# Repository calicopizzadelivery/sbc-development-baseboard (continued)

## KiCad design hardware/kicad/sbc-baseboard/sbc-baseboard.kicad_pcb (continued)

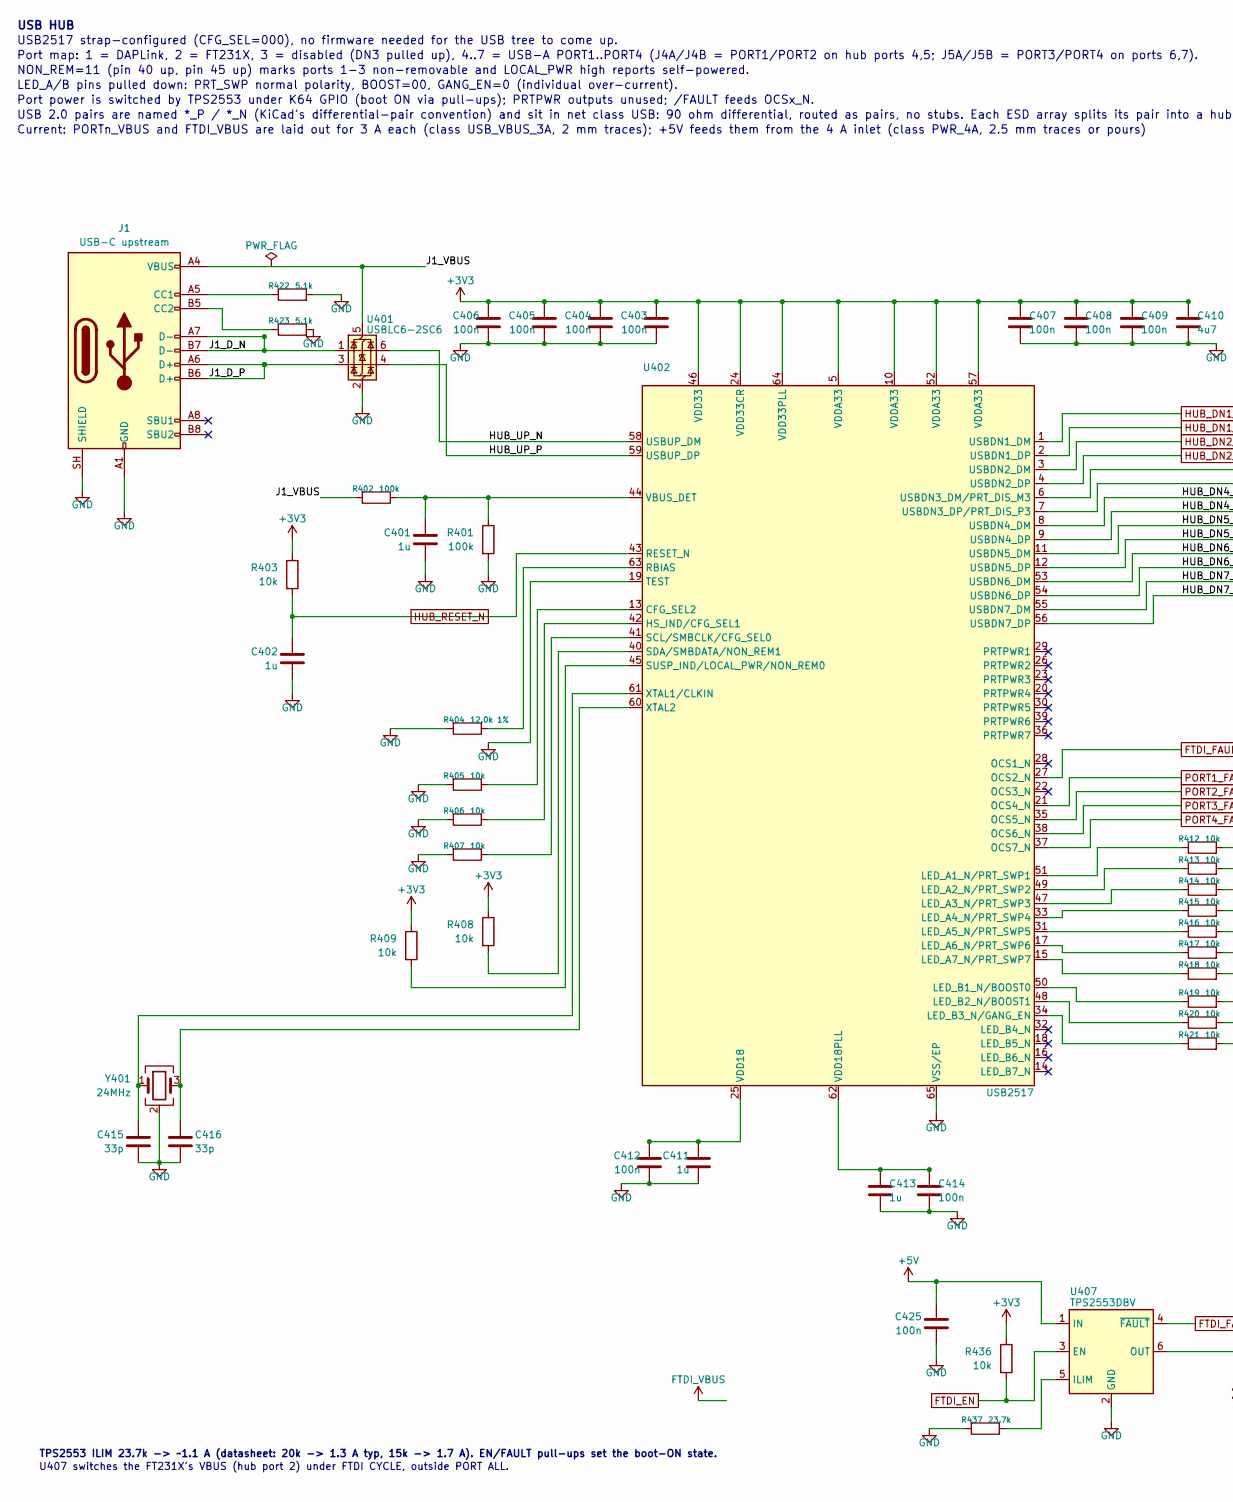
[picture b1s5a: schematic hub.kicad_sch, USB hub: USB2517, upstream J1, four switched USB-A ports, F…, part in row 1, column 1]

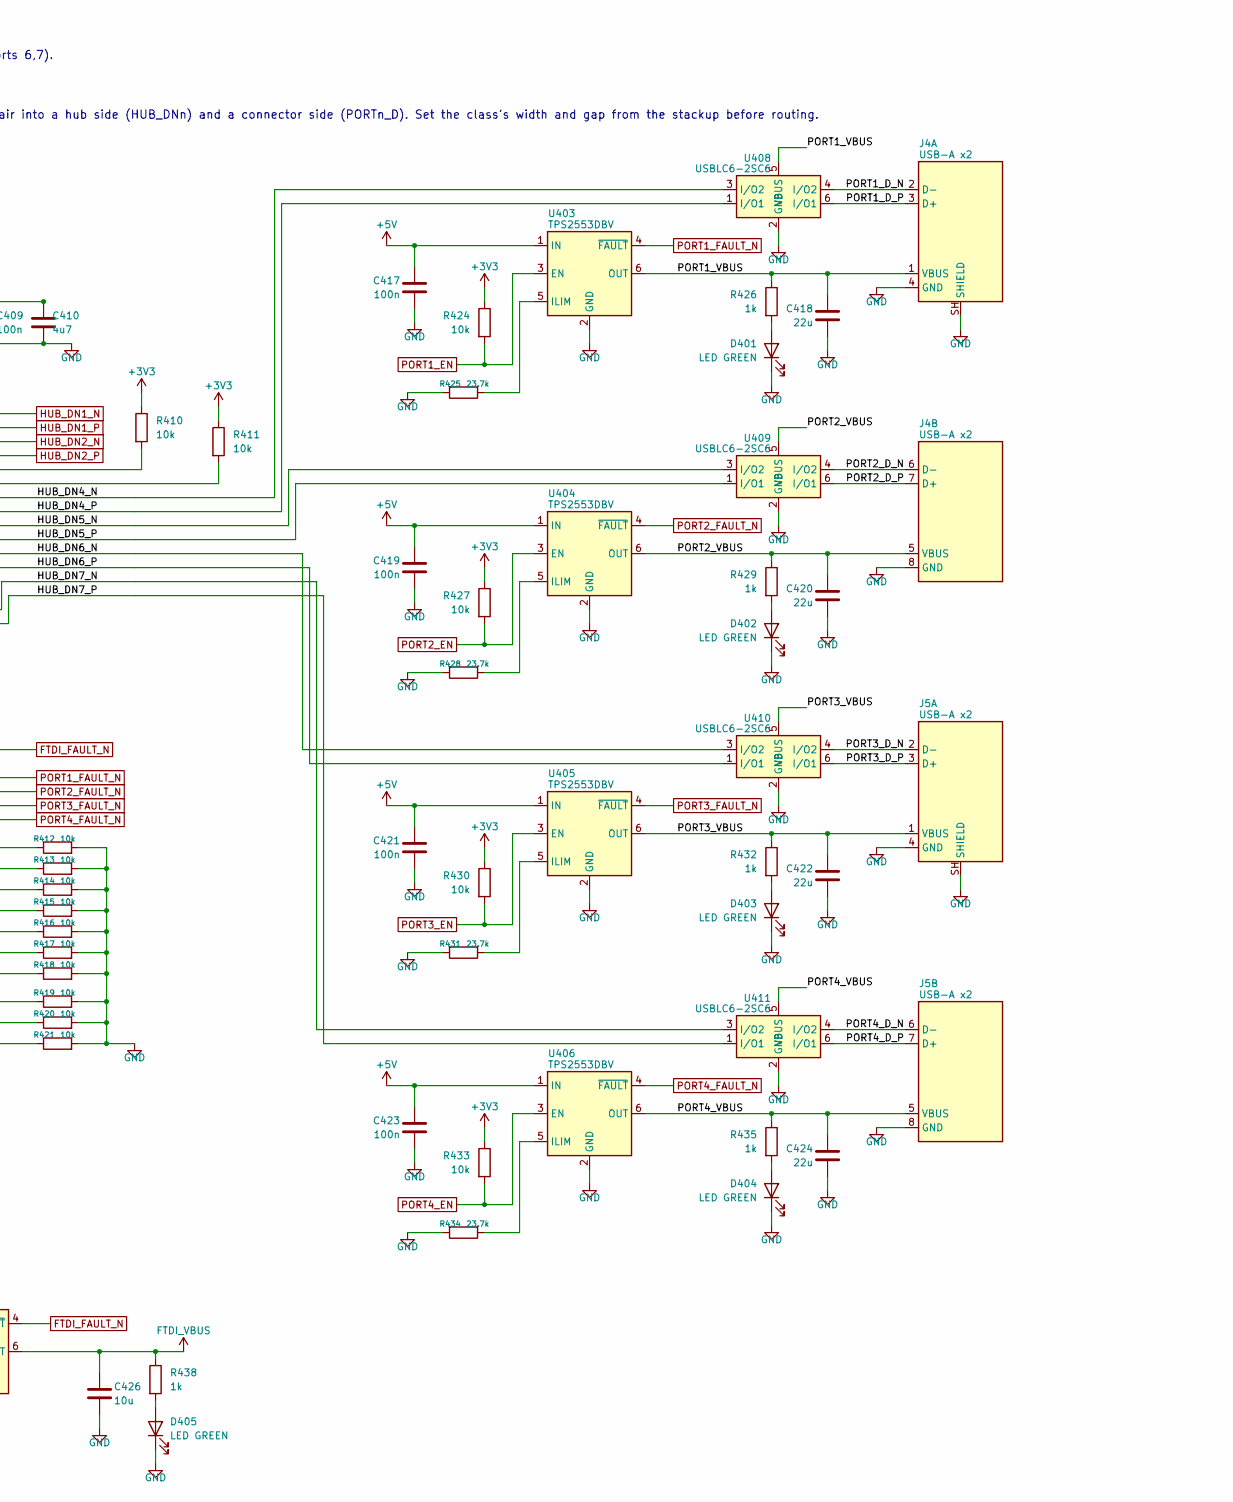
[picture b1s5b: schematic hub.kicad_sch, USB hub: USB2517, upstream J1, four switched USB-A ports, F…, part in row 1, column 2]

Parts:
C401, C402, C411, C413: 1u; C_0603_1608Metric
C403, C404, C405, C406, C407, C408, C409, C412, C414, C417, C419, C421, C423, C425: 100n; C_0603_1608Metric
C410: 4u7; C_0805_2012Metric
C415, C416: 33p; C_0603_1608Metric
C418, C420, C422, C424: 22u; C_1206_3216Metric
C426: 10u; C_0805_2012Metric
D401, D402, D403, D404, D405: LED GREEN; LED_0603_1608Metric
J1: USB-C upstream; USB_C_Receptacle_GCT_USB4105-xx-A_16P_TopMnt_Horizontal_Peg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
J4, J5: USB-A x2; USB_A_Wuerth_61400826021_Horizontal_Stacked
R401, R402: 100k; R_0603_1608Metric
R403, R405, R406, R407, R408, R409, R410, R411, R412, R413, R414, R415, R416, R417, R418, R419, R420, R421, R424, R427, R430, R433, R436: 10k; R_0603_1608Metric
R404: 12.0k 1%; R_0603_1608Metric
R422, R423: 5.1k; R_0603_1608Metric
R425, R428, R431, R434, R437: 23.7k; R_0603_1608Metric
R426, R429, R432, R435, R438: 1k; R_0603_1608Metric
U401, U408, U409, U410, U411: USBLC6-2SC6; SOT-23-6
U402: USB2517; QFN-64-1EP_9x9mm_P0.5mm_EP7.15x7.15mm
U403, U404, U405, U406, U407: TPS2553DBV; SOT-23-6
Y401: 24MHz; Crystal_SMD_3225-4Pin_3.2x2.5mm

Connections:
/USB hub/HUB_DN4_N: U402.8 (USBDN4_DM), U408.3 (I/O2)
/USB hub/HUB_DN4_P: U402.9 (USBDN4_DP), U408.1 (I/O1)
/USB hub/HUB_DN5_N: U402.11 (USBDN5_DM), U409.3 (I/O2)
/USB hub/HUB_DN5_P: U402.12 (USBDN5_DP), U409.1 (I/O1)
/USB hub/HUB_DN6_N: U402.53 (USBDN6_DM), U410.3 (I/O2)
/USB hub/HUB_DN6_P: U402.54 (USBDN6_DP), U410.1 (I/O1)
/USB hub/HUB_DN7_N: U402.55 (USBDN7_DM), U411.3 (I/O2)
/USB hub/HUB_DN7_P: U402.56 (USBDN7_DP), U411.1 (I/O1)
/USB hub/HUB_UP_N: U401.6 (I/O1), U402.58 (USBUP_DM)
/USB hub/HUB_UP_P: U401.4 (I/O2), U402.59 (USBUP_DP)
/USB hub/J1_D_N: J1.A7 (D-), J1.B7 (D-), U401.1 (I/O1)
/USB hub/J1_D_P: J1.A6 (D+), J1.B6 (D+), U401.3 (I/O2)
/USB hub/J1_VBUS: J1.A4 (VBUS), J1.A9 (VBUS), J1.B4 (VBUS), J1.B9 (VBUS), R402.2, U401.5 (VBUS)
/USB hub/PORT1_D_N: J4.2 (D-), U408.4 (I/O2)
/USB hub/PORT1_D_P: J4.3 (D+), U408.6 (I/O1)
/USB hub/PORT1_VBUS: C418.1, J4.1 (VBUS), R426.1, U403.6 (OUT), U408.5 (VBUS)
/USB hub/PORT2_D_N: J4.6 (D-), U409.4 (I/O2)
/USB hub/PORT2_D_P: J4.7 (D+), U409.6 (I/O1)
/USB hub/PORT2_VBUS: C420.1, J4.5 (VBUS), R429.1, U404.6 (OUT), U409.5 (VBUS)
/USB hub/PORT3_D_N: J5.2 (D-), U410.4 (I/O2)
/USB hub/PORT3_D_P: J5.3 (D+), U410.6 (I/O1)
/USB hub/PORT3_VBUS: C422.1, J5.1 (VBUS), R432.1, U405.6 (OUT), U410.5 (VBUS)
/USB hub/PORT4_D_N: J5.6 (D-), U411.4 (I/O2)
/USB hub/PORT4_D_P: J5.7 (D+), U411.6 (I/O1)
/USB hub/PORT4_VBUS: C424.1, J5.5 (VBUS), R435.1, U406.6 (OUT), U411.5 (VBUS)
FTDI_EN: R436.2, U407.3 (EN); also elsewhere on the board
FTDI_FAULT_N: U402.27 (OCS2_N), U407.4 (~FAULT); also elsewhere on the board
FTDI_VBUS: C426.1, R438.1, U407.6 (OUT); also elsewhere on the board
HUB_DN1_N: U402.1 (USBDN1_DM); also elsewhere on the board
HUB_DN1_P: U402.2 (USBDN1_DP); also elsewhere on the board
HUB_DN2_N: U402.3 (USBDN2_DM); also elsewhere on the board
HUB_DN2_P: U402.4 (USBDN2_DP); also elsewhere on the board
HUB_RESET_N: C402.1, R403.2, U402.43 (RESET_N); also elsewhere on the board
unnamed: D401.2 (A), R426.2
unnamed: D402.2 (A), R429.2
unnamed: D403.2 (A), R432.2
unnamed: D404.2 (A), R435.2
unnamed: D405.2 (A), R438.2
unnamed: J1.A5 (CC1), R422.1
unnamed: J1.B5 (CC2), R423.1
unnamed: R405.1, U402.13 (CFG_SEL2)
unnamed: R406.1, U402.42 (HS_IND/CFG_SEL1)
unnamed: R412.1, U402.51 (LED_A1_N/PRT_SWP1)
unnamed: R413.1, U402.49 (LED_A2_N/PRT_SWP2)
unnamed: R414.1, U402.47 (LED_A3_N/PRT_SWP3)
unnamed: R415.1, U402.33 (LED_A4_N/PRT_SWP4)
unnamed: R416.1, U402.31 (LED_A5_N/PRT_SWP5)
unnamed: R417.1, U402.17 (LED_A6_N/PRT_SWP6)
unnamed: R418.1, U402.15 (LED_A7_N/PRT_SWP7)
unnamed: R419.1, U402.50 (LED_B1_N/BOOST0)
unnamed: R420.1, U402.48 (LED_B2_N/BOOST1)
unnamed: R421.1, U402.34 (LED_B3_N/GANG_EN)
unnamed: R404.1, U402.63 (RBIAS)
unnamed: R407.1, U402.41 (SCL/SMBCLK/CFG_SEL0)
unnamed: R408.2, U402.40 (SDA/SMBDATA/NON_REM1)
unnamed: R409.2, U402.45 (SUSP_IND/LOCAL_PWR/NON_REM0)
unnamed: R410.2, U402.6 (USBDN3_DM/PRT_DIS_M3)
unnamed: R411.2, U402.7 (USBDN3_DP/PRT_DIS_P3)
unnamed: C401.1, R401.1, R402.1, U402.44 (VBUS_DET)
unnamed: C411.1, C412.1, U402.25 (VDD18)
unnamed: C413.1, C414.1, U402.62 (VDD18PLL)
unnamed: C415.1, U402.61 (XTAL1/CLKIN), Y401.1
unnamed: C416.1, U402.60 (XTAL2), Y401.3
unnamed: R425.1, U403.5 (ILIM)
unnamed: R428.1, U404.5 (ILIM)
unnamed: R431.1, U405.5 (ILIM)
unnamed: R434.1, U406.5 (ILIM)
unnamed: R437.1, U407.5 (ILIM)
PORT1_EN: R424.2, U403.3 (EN); also elsewhere on the board
PORT1_FAULT_N: U402.21 (OCS4_N), U403.4 (~FAULT); also elsewhere on the board
PORT2_EN: R427.2, U404.3 (EN); also elsewhere on the board
PORT2_FAULT_N: U402.35 (OCS5_N), U404.4 (~FAULT); also elsewhere on the board
PORT3_EN: R430.2, U405.3 (EN); also elsewhere on the board
PORT3_FAULT_N: U402.38 (OCS6_N), U405.4 (~FAULT); also elsewhere on the board
PORT4_EN: R433.2, U406.3 (EN); also elsewhere on the board
PORT4_FAULT_N: U402.37 (OCS7_N), U406.4 (~FAULT); also elsewhere on the board

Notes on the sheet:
USB HUB
USB2517 strap-configured (CFG_SEL=000), no firmware needed for the USB tree to come up.
Port map: 1 = DAPLink, 2 = FT231X, 3 = disabled (DN3 pulled up), 4..7 = USB-A PORT1..PORT4 (J4A/J4B = PORT1/PORT2 on hub ports 4,5; J5A/J5B = PORT3/PORT4 on ports 6,7).
NON_REM=11 (pin 40 up, pin 45 up) marks ports 1-3 non-removable and LOCAL_PWR high reports self-powered.
LED_A/B pins pulled down: PRT_SWP normal polarity, BOOST=00, GANG_EN=0 (individual over-current).
Port power is switched by TPS2553 under K64 GPIO (boot ON via pull-ups); PRTPWR outputs unused; /FAULT feeds OCSx_N.
USB 2.0 pairs are named *_P / *_N (KiCad's differential-pair convention) and sit in net class USB: 90 ohm differential, routed as pairs, no stubs. Each ESD array splits its pair into a hub side (HUB_DNn) and a connector side (PORTn_D). Set the class's width and gap from the stackup before routing.
Current: PORTn_VBUS and FTDI_VBUS are laid out for 3 A each (class USB_VBUS_3A, 2 mm traces); +5V feeds them from the 4 A inlet (class PWR_4A, 2.5 mm traces or pours)
TPS2553 ILIM 23.7k -> ~1.1 A (datasheet: 20k -> 1.3 A typ, 15k -> 1.7 A). EN/FAULT pull-ups set the boot-ON state.
U407 switches the FT231X's VBUS (hub port 2) under FTDI CYCLE, outside PORT ALL.

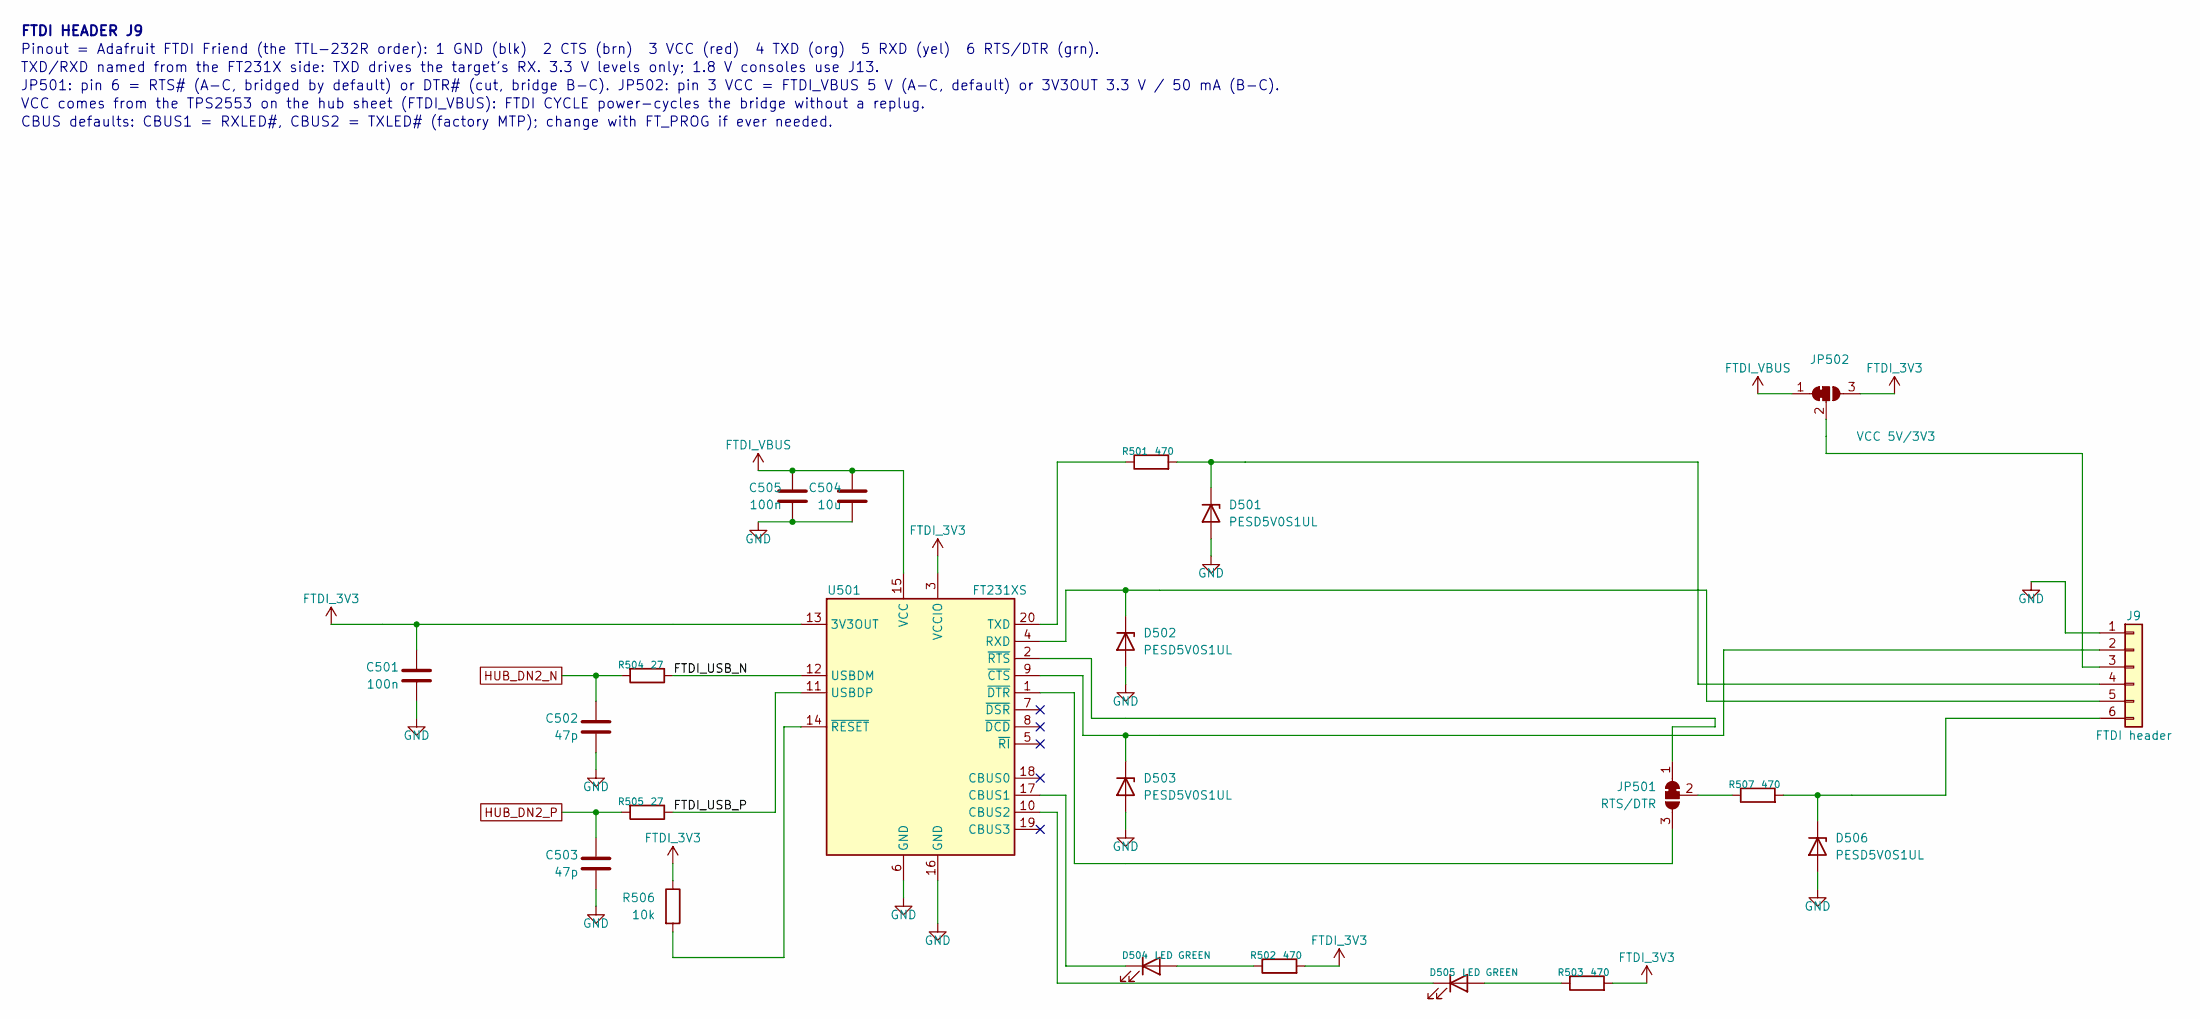
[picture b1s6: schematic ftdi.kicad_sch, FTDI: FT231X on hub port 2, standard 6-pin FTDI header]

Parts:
C501, C505: 100n; C_0603_1608Metric
C502, C503: 47p; C_0603_1608Metric
C504: 10u; C_0805_2012Metric
D501, D502, D503, D506: PESD5V0S1UL; D_SOD-882
D504, D505: LED GREEN; LED_0603_1608Metric
J9: FTDI header; PinHeader_1x06_P2.54mm_Horizontal
JP501: RTS/DTR; SolderJumper-3_P1.3mm_Bridged12_RoundedPad1.0x1.5mm
JP502: VCC 5V/3V3; SolderJumper-3_P1.3mm_Bridged12_RoundedPad1.0x1.5mm
R501, R502, R503, R507: 470; R_0603_1608Metric
R504, R505: 27; R_0603_1608Metric
R506: 10k; R_0603_1608Metric
U501: FT231XS; SSOP-20_3.9x8.7mm_P0.635mm

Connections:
/FTDI/FTDI_USB_N: R504.1, U501.12 (USBDM)
/FTDI/FTDI_USB_P: R505.1, U501.11 (USBDP)
FTDI_3V3: C501.1, JP502.3 (B), R502.2, R503.2, R506.1, U501.3 (VCCIO), U501.13 (3V3OUT)
FTDI_VBUS: C504.1, C505.1, JP502.1 (A), U501.15 (VCC); also elsewhere on the board
HUB_DN2_N: C502.1, R504.2; also elsewhere on the board
HUB_DN2_P: C503.1, R505.2; also elsewhere on the board
unnamed: D501.1 (K), J9.4, R501.2
unnamed: D502.1 (K), J9.5, U501.4 (RXD)
unnamed: D503.1 (K), J9.2, U501.9 (~CTS)
unnamed: D504.2 (A), R502.1
unnamed: D504.1 (K), U501.17 (CBUS1)
unnamed: D505.2 (A), R503.1
unnamed: D505.1 (K), U501.10 (CBUS2)
unnamed: D506.1 (K), J9.6, R507.2
unnamed: J9.3, JP502.2 (C)
unnamed: JP501.1 (A), U501.2 (~RTS)
unnamed: JP501.3 (B), U501.1 (~DTR)
unnamed: JP501.2 (C), R507.1
unnamed: R501.1, U501.20 (TXD)
unnamed: R506.2, U501.14 (~RESET)

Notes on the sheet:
FTDI HEADER J9
Pinout = Adafruit FTDI Friend (the TTL-232R order): 1 GND (blk) 2 CTS (brn) 3 VCC (red) 4 TXD (org) 5 RXD (yel) 6 RTS/DTR (grn).
TXD/RXD named from the FT231X side: TXD drives the target's RX. 3.3 V levels only; 1.8 V consoles use J13.
JP501: pin 6 = RTS# (A-C, bridged by default) or DTR# (cut, bridge B-C). JP502: pin 3 VCC = FTDI_VBUS 5 V (A-C, default) or 3V3OUT 3.3 V / 50 mA (B-C).
VCC comes from the TPS2553 on the hub sheet (FTDI_VBUS): FTDI CYCLE power-cycles the bridge without a replug.
CBUS defaults: CBUS1 = RXLED#, CBUS2 = TXLED# (factory MTP); change with FT_PROG if ever needed.

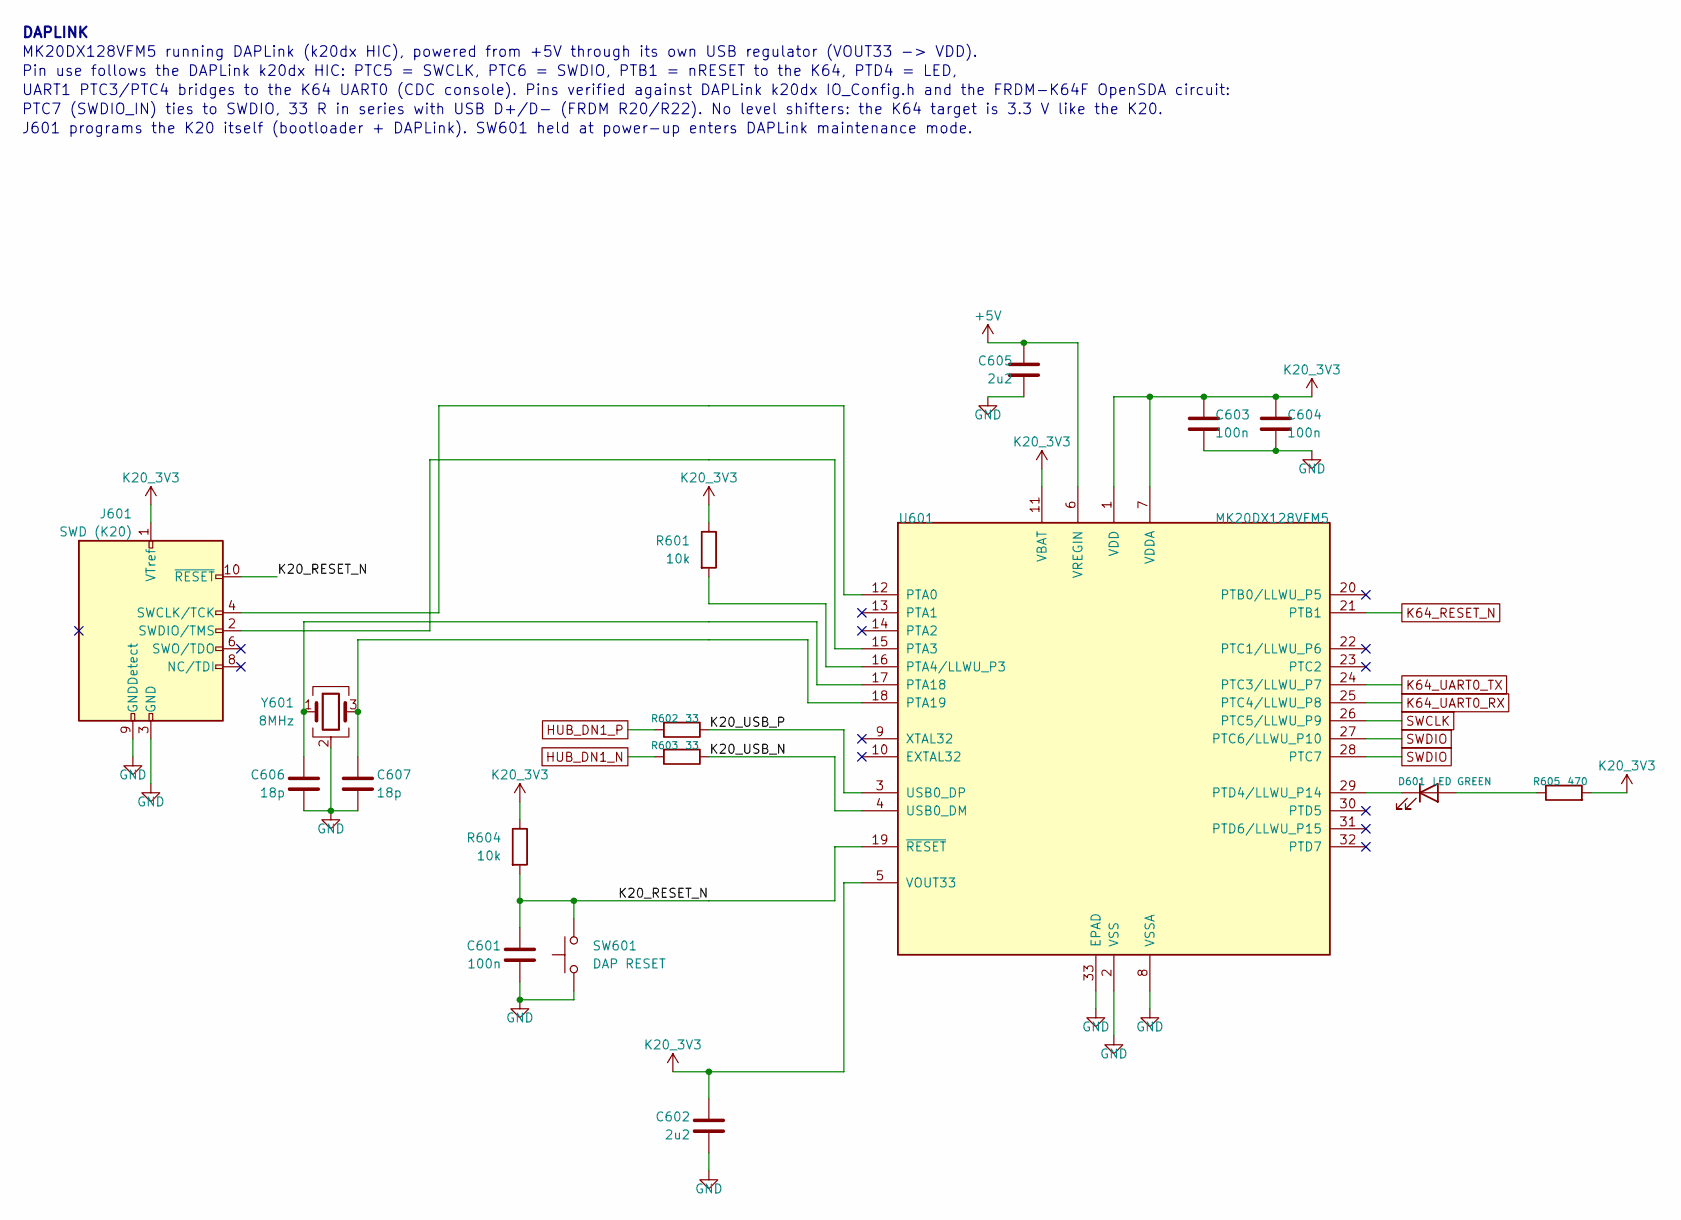
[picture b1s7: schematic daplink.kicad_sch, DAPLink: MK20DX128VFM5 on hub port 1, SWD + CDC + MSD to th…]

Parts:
C601, C603, C604: 100n; C_0603_1608Metric
C602, C605: 2u2; C_0603_1608Metric
C606, C607: 18p; C_0603_1608Metric
D601: LED GREEN; LED_0603_1608Metric
J601: SWD (K20); PinHeader_2x05_P1.27mm_Vertical
R601, R604: 10k; R_0603_1608Metric
R602, R603: 33; R_0603_1608Metric
R605: 470; R_0603_1608Metric
SW601: DAP RESET; SW_SPST_PTS645Sx43SMTR92
U601: MK20DX128VFM5; QFN-32-1EP_5x5mm_P0.5mm_EP3.45x3.45mm
Y601: 8MHz; Crystal_SMD_3225-4Pin_3.2x2.5mm

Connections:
/DAPLink/K20_RESET_N: C601.1, J601.10 (~RESET), R604.2, SW601.2, U601.19 (~RESET)
/DAPLink/K20_USB_N: R603.1, U601.4 (USB0_DM)
/DAPLink/K20_USB_P: R602.1, U601.3 (USB0_DP)
HUB_DN1_N: R603.2; also elsewhere on the board
HUB_DN1_P: R602.2; also elsewhere on the board
K20_3V3: C602.1, C603.1, C604.1, J601.1 (VTref), R601.1, R604.1, R605.2, U601.1 (VDD), U601.5 (VOUT33), U601.7 (VDDA), U601.11 (VBAT)
K64_RESET_N: U601.21 (PTB1); also elsewhere on the board
K64_UART0_RX: U601.25 (PTC4/LLWU_P8); also elsewhere on the board
K64_UART0_TX: U601.24 (PTC3/LLWU_P7); also elsewhere on the board
unnamed: D601.2 (A), R605.1
unnamed: D601.1 (K), U601.29 (PTD4/LLWU_P14)
unnamed: J601.4 (SWCLK/TCK), U601.12 (PTA0)
unnamed: J601.2 (SWDIO/TMS), U601.15 (PTA3)
unnamed: R601.2, U601.16 (PTA4/LLWU_P3)
unnamed: C606.1, U601.17 (PTA18), Y601.1
unnamed: C607.1, U601.18 (PTA19), Y601.3
SWCLK: U601.26 (PTC5/LLWU_P9); also elsewhere on the board
SWDIO: U601.27 (PTC6/LLWU_P10), U601.28 (PTC7); also elsewhere on the board

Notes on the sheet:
DAPLINK
MK20DX128VFM5 running DAPLink (k20dx HIC), powered from +5V through its own USB regulator (VOUT33 -> VDD).
Pin use follows the DAPLink k20dx HIC: PTC5 = SWCLK, PTC6 = SWDIO, PTB1 = nRESET to the K64, PTD4 = LED,
UART1 PTC3/PTC4 bridges to the K64 UART0 (CDC console). Pins verified against DAPLink k20dx IO_Config.h and the FRDM-K64F OpenSDA circuit:
PTC7 (SWDIO_IN) ties to SWDIO, 33 R in series with USB D+/D- (FRDM R20/R22). No level shifters: the K64 target is 3.3 V like the K20.
J601 programs the K20 itself (bootloader + DAPLink). SW601 held at power-up enters DAPLink maintenance mode.

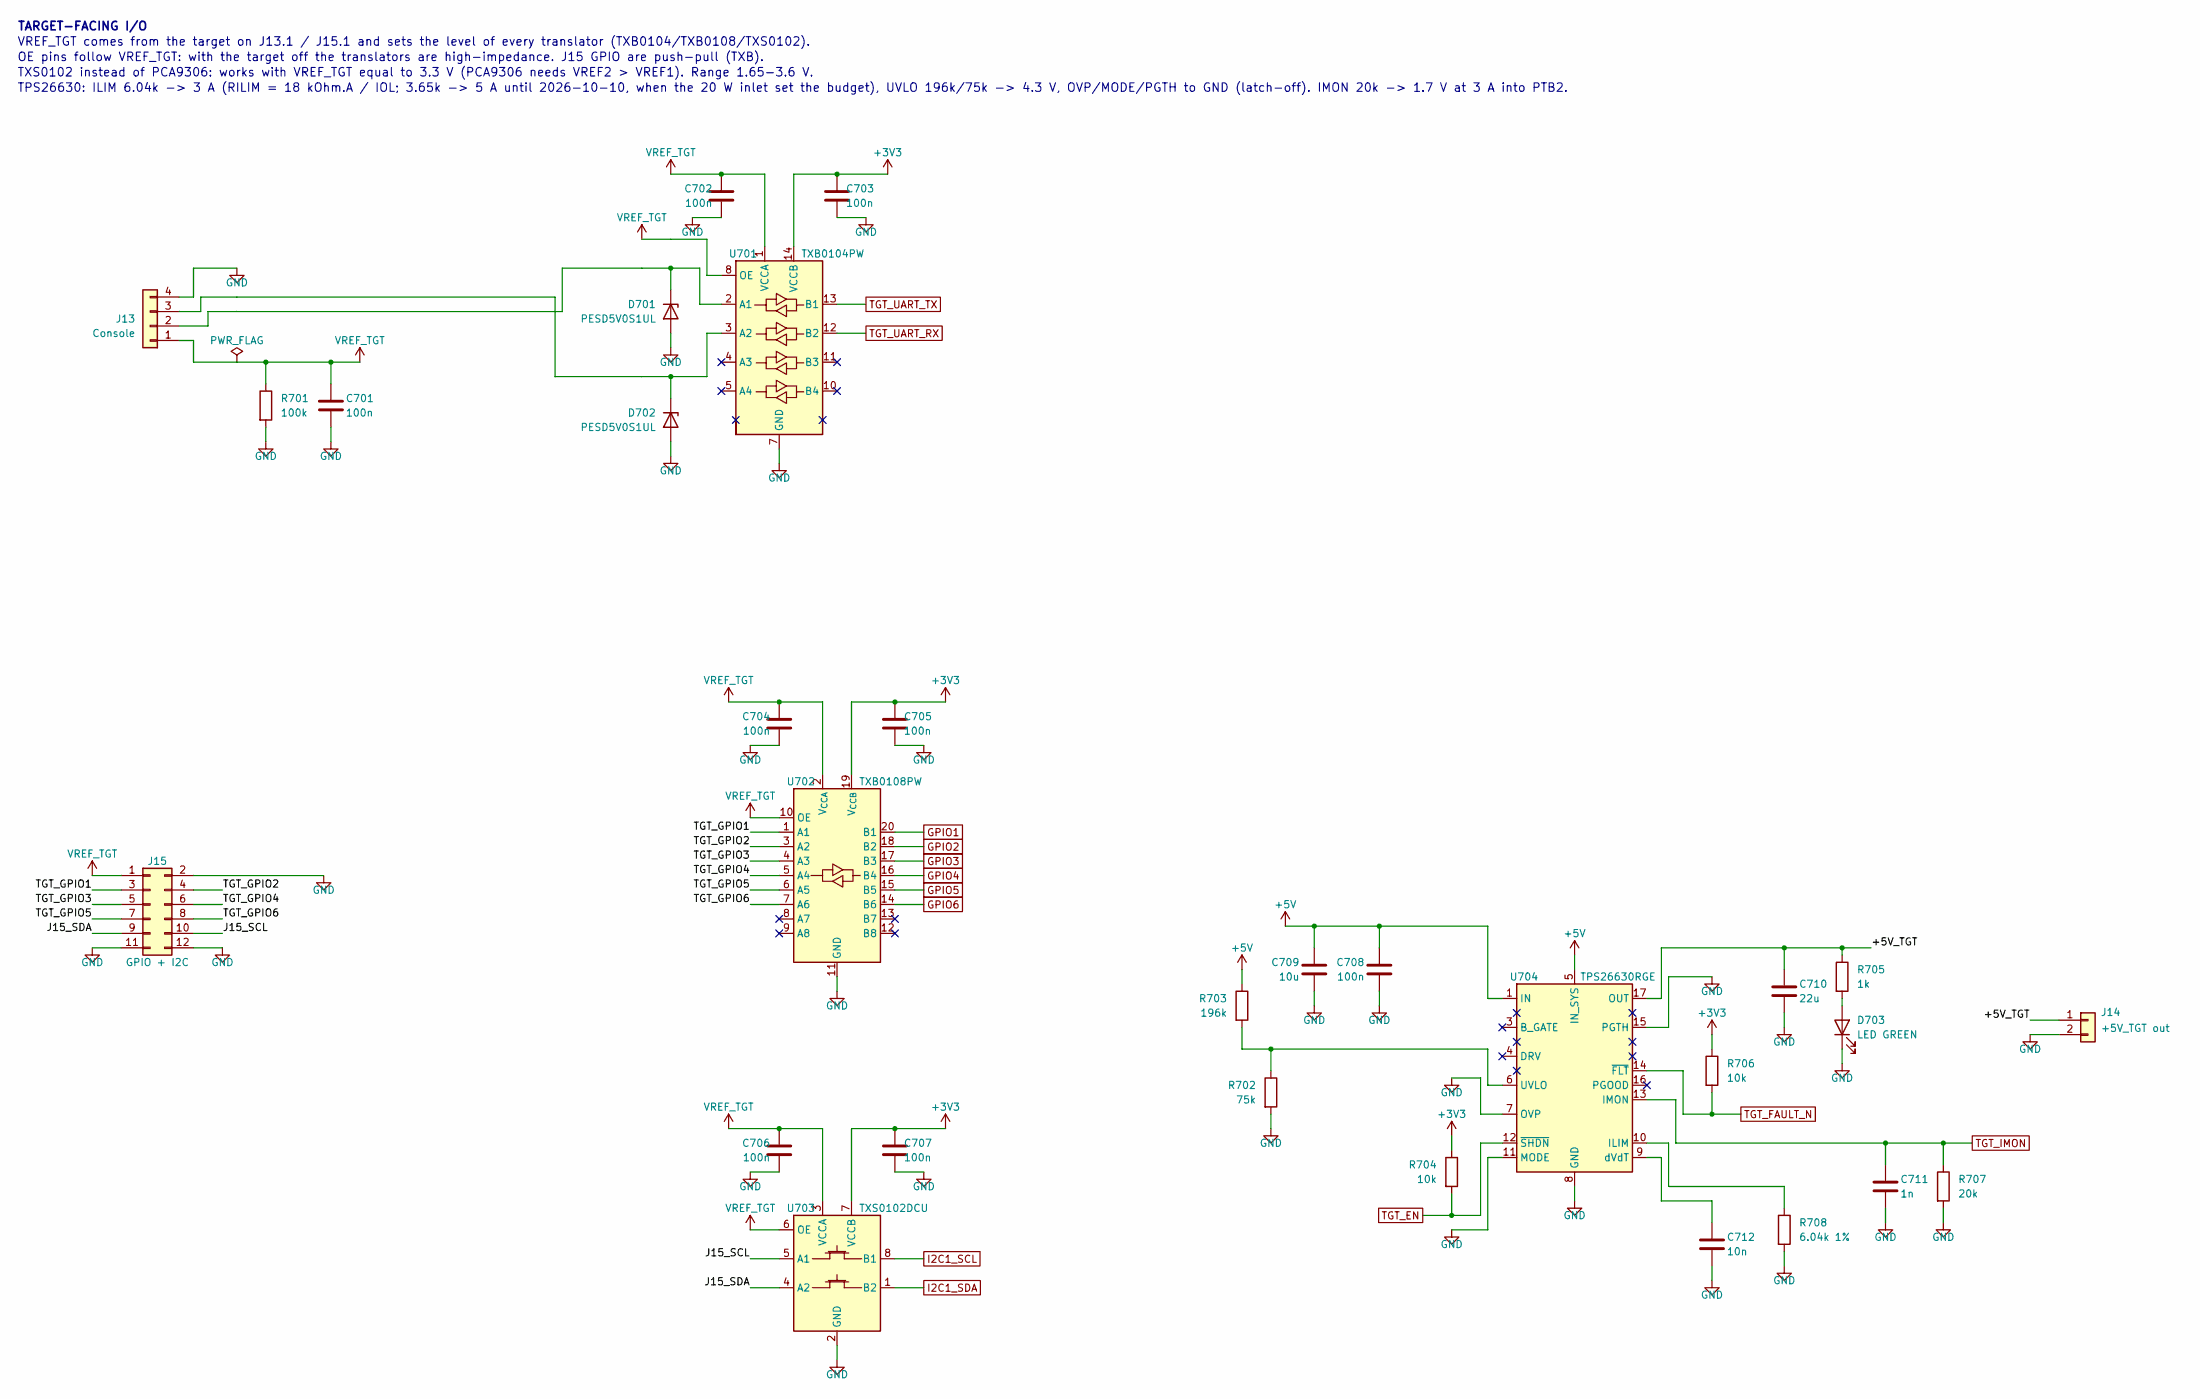
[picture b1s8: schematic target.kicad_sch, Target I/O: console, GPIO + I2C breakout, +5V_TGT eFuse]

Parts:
C701, C702, C703, C704, C705, C706, C707, C708: 100n; C_0603_1608Metric
C709: 10u; C_0805_2012Metric
C710: 22u; C_1206_3216Metric
C711: 1n; C_0603_1608Metric
C712: 10n; C_0603_1608Metric
D701, D702: PESD5V0S1UL; D_SOD-882
D703: LED GREEN; LED_0603_1608Metric
J13: Console; PhoenixContact_MC_1,5_4-G-3.5_1x04_P3.50mm_Horizontal
J14: +5V_TGT out; PhoenixContact_MSTBA_2,5_2-G-5,08_1x02_P5.08mm_Horizontal
J15: GPIO + I2C; PinHeader_2x06_P2.54mm_Vertical
R701: 100k; R_0603_1608Metric
R702: 75k; R_0603_1608Metric
R703: 196k; R_0603_1608Metric
R704, R706: 10k; R_0603_1608Metric
R705: 1k; R_0603_1608Metric
R707: 20k; R_0603_1608Metric
R708: 6.04k 1%; R_0603_1608Metric
U701: TXB0104PW; TSSOP-14_4.4x5mm_P0.65mm
U702: TXB0108PW; TSSOP-20_4.4x6.5mm_P0.65mm
U703: TXS0102DCU; VSSOP-8_2.3x2mm_P0.5mm
U704: TPS26630RGE; Texas_RGE0024H_VQFN-24-1EP_4x4mm_P0.5mm_EP2.7x2.7mm_Thermal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

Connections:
/Target I/O/+5V_TGT: C710.1, J14.1, R705.1, U704.17 (OUT), U704.18 (OUT)
/Target I/O/J15_SCL: J15.10, U703.5 (A1)
/Target I/O/J15_SDA: J15.9, U703.4 (A2)
/Target I/O/TGT_GPIO1: J15.3, U702.1 (A1)
/Target I/O/TGT_GPIO2: J15.4, U702.3 (A2)
/Target I/O/TGT_GPIO3: J15.5, U702.4 (A3)
/Target I/O/TGT_GPIO4: J15.6, U702.5 (A4)
/Target I/O/TGT_GPIO5: J15.7, U702.6 (A5)
/Target I/O/TGT_GPIO6: J15.8, U702.7 (A6)
GPIO1: U702.20 (B1); also elsewhere on the board
GPIO2: U702.18 (B2); also elsewhere on the board
GPIO3: U702.17 (B3); also elsewhere on the board
GPIO4: U702.16 (B4); also elsewhere on the board
GPIO5: U702.15 (B5); also elsewhere on the board
GPIO6: U702.14 (B6); also elsewhere on the board
I2C1_SCL: U703.8 (B1); also elsewhere on the board
I2C1_SDA: U703.1 (B2); also elsewhere on the board
unnamed: D701.1 (K), J13.2, U701.2 (A1)
unnamed: D702.1 (K), J13.3, U701.3 (A2)
unnamed: D703.2 (A), R705.2
unnamed: R708.1, U704.10 (ILIM)
unnamed: R702.1, R703.2, U704.6 (UVLO)
unnamed: C712.1, U704.9 (dVdT)
TGT_EN: R704.2, U704.12 (~SHDN); also elsewhere on the board
TGT_FAULT_N: R706.2, U704.14 (~FLT); also elsewhere on the board
TGT_IMON: C711.1, R707.1, U704.13 (IMON); also elsewhere on the board
TGT_UART_RX: U701.12 (B2); also elsewhere on the board
TGT_UART_TX: U701.13 (B1); also elsewhere on the board
VREF_TGT: C701.1, C702.1, C704.1, C706.1, J13.1, J15.1, R701.1, U701.1 (VCCA), U701.8 (OE), U702.2 (V_{CCA}), U702.10 (OE), U703.3 (VCCA), U703.6 (OE)

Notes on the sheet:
TARGET-FACING I/O
VREF_TGT comes from the target on J13.1 / J15.1 and sets the level of every translator (TXB0104/TXB0108/TXS0102).
OE pins follow VREF_TGT: with the target off the translators are high-impedance. J15 GPIO are push-pull (TXB).
TXS0102 instead of PCA9306: works with VREF_TGT equal to 3.3 V (PCA9306 needs VREF2 > VREF1). Range 1.65-3.6 V.
TPS26630: ILIM 6.04k -> 3 A (RILIM = 18 kOhm.A / IOL; 3.65k -> 5 A until 2026-10-10, when the 20 W inlet set the budget), UVLO 196k/75k -> 4.3 V, OVP/MODE/PGTH to GND (latch-off). IMON 20k -> 1.7 V at 3 A into PTB2.

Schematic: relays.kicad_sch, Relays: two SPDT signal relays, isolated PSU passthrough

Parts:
D801, D803, D805, D807: 1N4148W; D_SOD-123
D802, D804, D806: LED RED; LED_0603_1608Metric
J11, J12: COM/NO/NC; PhoenixContact_MC_1,5_3-G-3.5_1x03_P3.50mm_Horizontal
J18: PSU in (isolated); PhoenixContact_MSTBA_2,5_2-G-5,08_1x02_P5.08mm_Horizontal
J19: PSU out (isolated); PhoenixContact_MSTBA_2,5_2-G-5,08_1x02_P5.08mm_Horizontal
K801, K802: G6K-2F-Y DC5; Relay_DPDT_Omron_G6K-2F-Y
K803: JW1FSN-DC5V; Relay_SPDT_Panasonic_JW1_FormC
Q801, Q802: 2N7002; SOT-23
Q803: AO3400A; SOT-23
R801, R804, R807: 2.2k; R_0603_1608Metric
R802, R805, R808: 100k; R_0603_1608Metric
R803, R806, R809: 1k; R_0603_1608Metric
R810, R811: 1.8k; R_1206_3216Metric
R812: 10k; R_0603_1608Metric
U801: LTV-817; DIP-4_W7.62mm

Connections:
/Relays/PSU_SENSE: D807.1 (K), R810.1, U801.1
/Relays/PSU_SENSE_R: R810.2, R811.1
/Relays/PSU_VOUT: J19.1, K803.4 (NO)
/Relays/PSU_VP: J18.1, K803.6 (COM), R811.2
unnamed: D801.2 (A), D802.1 (K), K801.1, Q801.3 (D)
unnamed: D802.2 (A), R801.2
unnamed: D803.2 (A), D804.1 (K), K802.1, Q802.3 (D)
unnamed: D804.2 (A), R804.2
unnamed: D805.2 (A), D806.1 (K), K803.8 (COIL-), Q803.3 (D)
unnamed: D806.2 (A), R807.2
unnamed: J11.1, K801.3
unnamed: J11.2, K801.4
unnamed: J11.3, K801.2
unnamed: J12.1, K802.3
unnamed: J12.2, K802.4
unnamed: J12.3, K802.2
unnamed: Q801.1 (G), R802.1, R803.1
unnamed: Q802.1 (G), R805.1, R806.1
unnamed: Q803.1 (G), R808.1, R809.1
PSU_GND: D807.2 (A), J18.2, J19.2, U801.2
PSU_PRESENT_N: R812.2, U801.4; also elsewhere on the board
RLY1_DRV: R803.2; also elsewhere on the board
RLY2_DRV: R806.2; also elsewhere on the board
RLY_PSU_DRV: R809.2; also elsewhere on the board

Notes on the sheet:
RELAYS AND PASSTHROUGH
K801/K802 G6K-2F-Y: pole 1 used (COM 3, NC 2, NO 4), pole 2 unused. Coils boot de-energized (gate pull-downs).
Red LEDs sit across each coil and show the energized state. Flyback 1N4148W on every coil.
Passthrough J18 -> K803 (NO contact) -> J19 on nets PSU_VP / PSU_VOUT / PSU_GND that touch no board net: PSU_GND is its own ground.
Only the optocoupler's emitter sits across the passthrough, sized for 5-30 V. No indicator LED there.
K803 JW1FSN pad map COM=6 NO=4 NC=2: VERIFY against the Panasonic terminal drawing before fab.
Current: the passthrough J18 -> K803 -> J19 (PSU_VP, PSU_VOUT, PSU_GND) is laid out for 3 A continuous: class PSU_3A, 2 mm traces or pours, two vias per layer change.
Opto LED: 2x1.8k 1206 in series, 1 mA at 5 V, 8 mA / 0.12 W each at 30 V. The antiparallel 1N4148W protects a reversed PSU.
PSU_PRESENT_N is active low at the K64.

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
